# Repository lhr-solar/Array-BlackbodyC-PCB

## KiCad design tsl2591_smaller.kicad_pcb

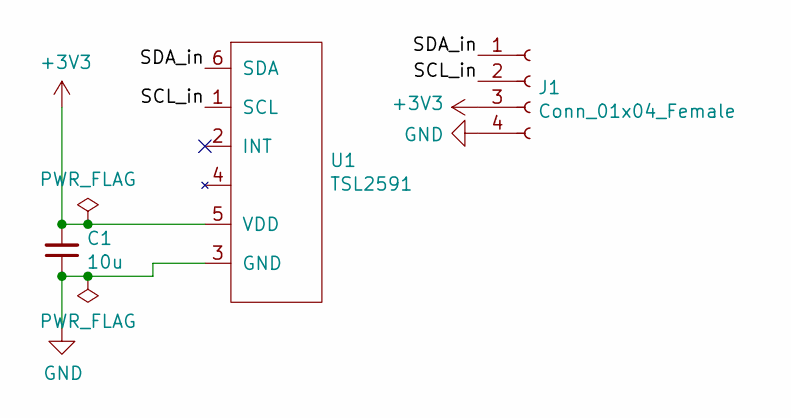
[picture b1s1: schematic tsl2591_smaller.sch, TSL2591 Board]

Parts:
C1: 10u; R_0805
J1: Conn_01x04_Female; PinHeader_2x02_P2.54mm_Vertical_SMD
U1: TSL2591; tsl2591

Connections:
+3V3: C1.2, J1.3, U1.5 (VDD)
/SCL_in: J1.2, U1.1 (SCL)
/SDA_in: J1.1, U1.6 (SDA)
GND: C1.1, J1.4, U1.3 (GND)

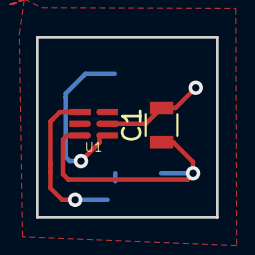
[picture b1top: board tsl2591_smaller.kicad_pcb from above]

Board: 2 copper layers, 10.0 x 10.0 mm, 3 parts (1 on the bottom side), 4 nets.

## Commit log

2022-04-09 init commit
